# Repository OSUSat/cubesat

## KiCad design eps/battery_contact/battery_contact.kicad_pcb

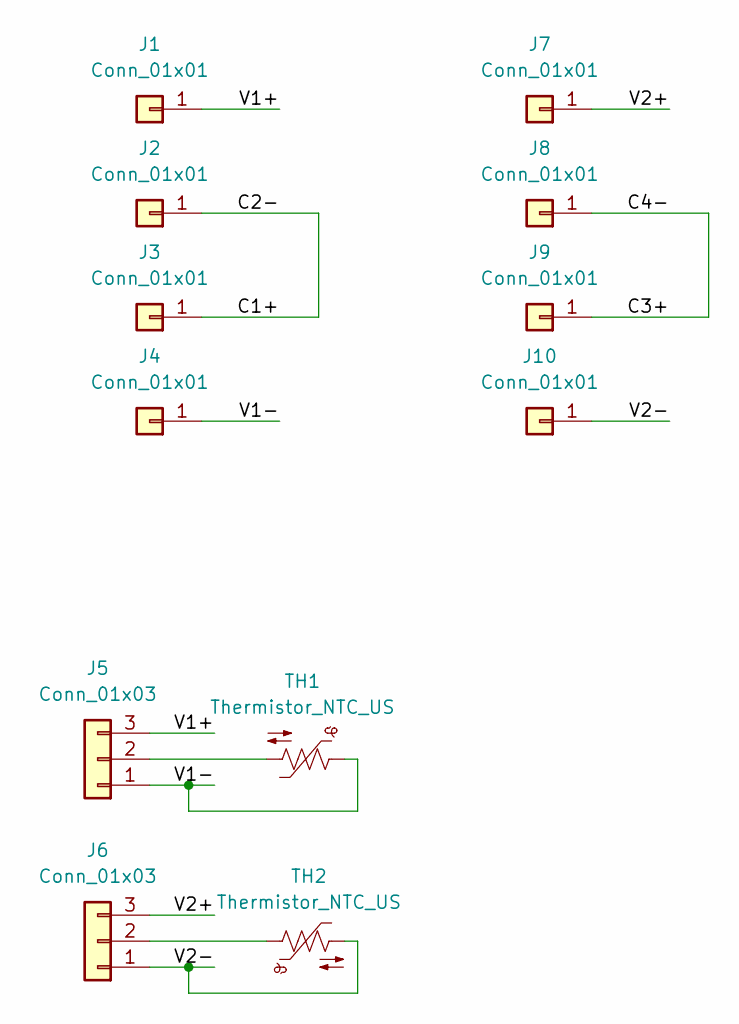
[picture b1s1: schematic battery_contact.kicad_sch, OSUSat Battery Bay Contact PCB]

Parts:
J1, J2, J3, J4, J7, J8, J9, J10: Conn_01x01; BAT_FB07
J5, J6: Conn_01x03; JST_PH_B3B-PH-K_1x03_P2.00mm_Vertical
TH1, TH2: Thermistor_NTC_US; R_0402_1005Metric

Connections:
/C1+: J2.1 (Pin_1_1), J3.1 (Pin_1_1)
/C3+: J8.1 (Pin_1_1), J9.1 (Pin_1_1)
/V1+: J1.1 (Pin_1_1), J5.3
/V1-: J4.1 (Pin_1_1), J5.1, TH1.1
/V2+: J6.3, J7.1 (Pin_1_1)
/V2-: J6.1, J10.1 (Pin_1_1), TH2.2
unnamed: J5.2, TH1.2
unnamed: J6.2, TH2.1

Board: 2 copper layers, 12 parts (0 on the bottom side), 8 nets, no tracks yet.

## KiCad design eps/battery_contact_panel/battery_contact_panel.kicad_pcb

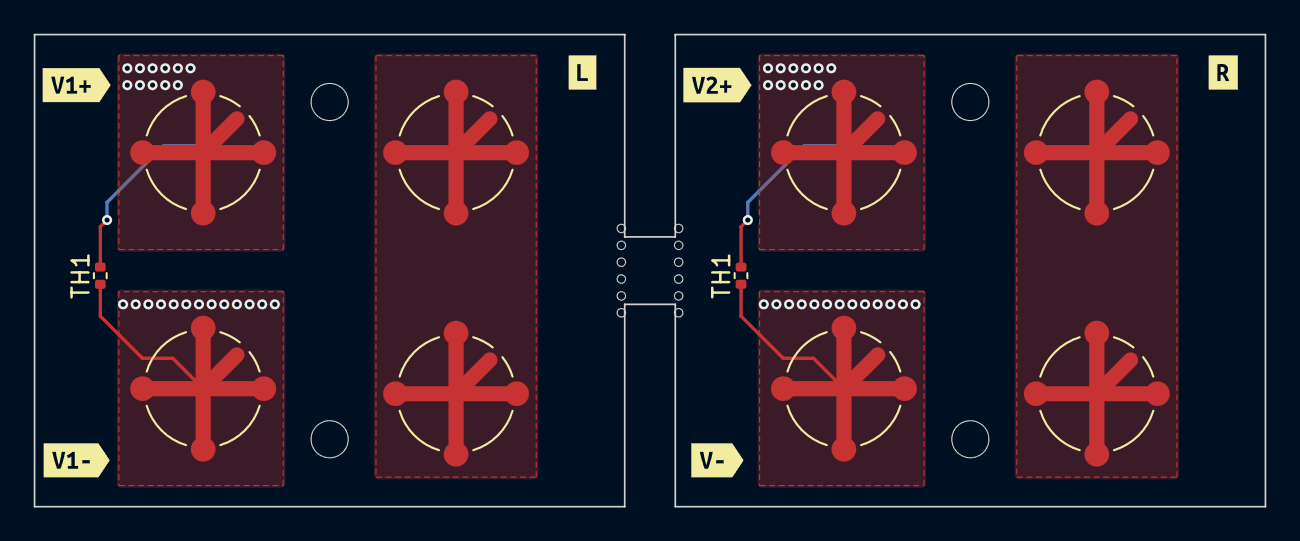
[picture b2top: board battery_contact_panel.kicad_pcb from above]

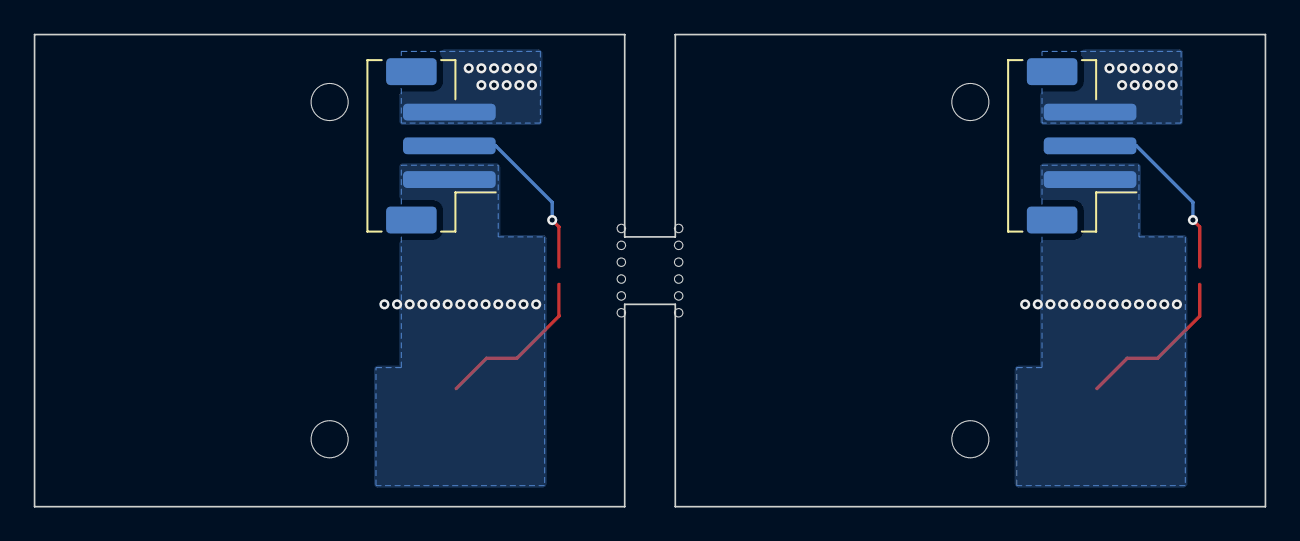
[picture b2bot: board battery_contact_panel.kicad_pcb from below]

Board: 2 copper layers, 73.0 x 28.0 mm, 34 parts (2 on the bottom side), 8 nets.

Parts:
H1, H1#2, H2, H2#2: MountingHole; MountingHole_2.2mm_M2
J1, J1#2, J2, J2#2, J4, J4#2, J7, J7#2: Conn_01x01; BAT_FB07
J5, J5#2: Conn_01x03; JST_PH_B3B-PH-SM4-TB_1x03-1MP_P2.00mm_Vertical
KiKit_MB_1_1, KiKit_MB_1_2, KiKit_MB_1_3, KiKit_MB_1_4, KiKit_MB_1_5, KiKit_MB_1_6, KiKit_MB_2_1, KiKit_MB_2_2, KiKit_MB_2_3, KiKit_MB_2_4, KiKit_MB_2_5, KiKit_MB_2_6: NPTH
TH1, TH1#2: Thermistor_NTC_US; R_0402_1005Metric
kibuzzard-6A263C7A: G***; kibuzzard-6A263C7A
kibuzzard-6A263D29: G***; kibuzzard-6A263D29
kibuzzard-6A2907CC: G***; kibuzzard-6A2907CC
kibuzzard-6A2907D5: G***; kibuzzard-6A2907D5
kibuzzard-6A2907E9: G***; kibuzzard-6A2907E9
kibuzzard-6A2907EF: G***; kibuzzard-6A2907EF

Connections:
Board_0-/C1+: J2.1 (Pin_1_1), J7#2.1 (Pin_1_1)
Board_0-/V1+: J1#2.1 (Pin_1_1), J5.3
Board_0-/V1-: J4#2.1 (Pin_1_1), J5.1, TH1.1
Board_0-Net-(J5-Pin_2): J5.2, TH1.2
Board_1-/C1+: J2#2.1 (Pin_1_1), J7.1 (Pin_1_1)
Board_1-/V1+: J1.1 (Pin_1_1), J5#2.3
Board_1-/V1-: J4.1 (Pin_1_1), J5#2.1, TH1#2.1
Board_1-Net-(J5-Pin_2): J5#2.2, TH1#2.2

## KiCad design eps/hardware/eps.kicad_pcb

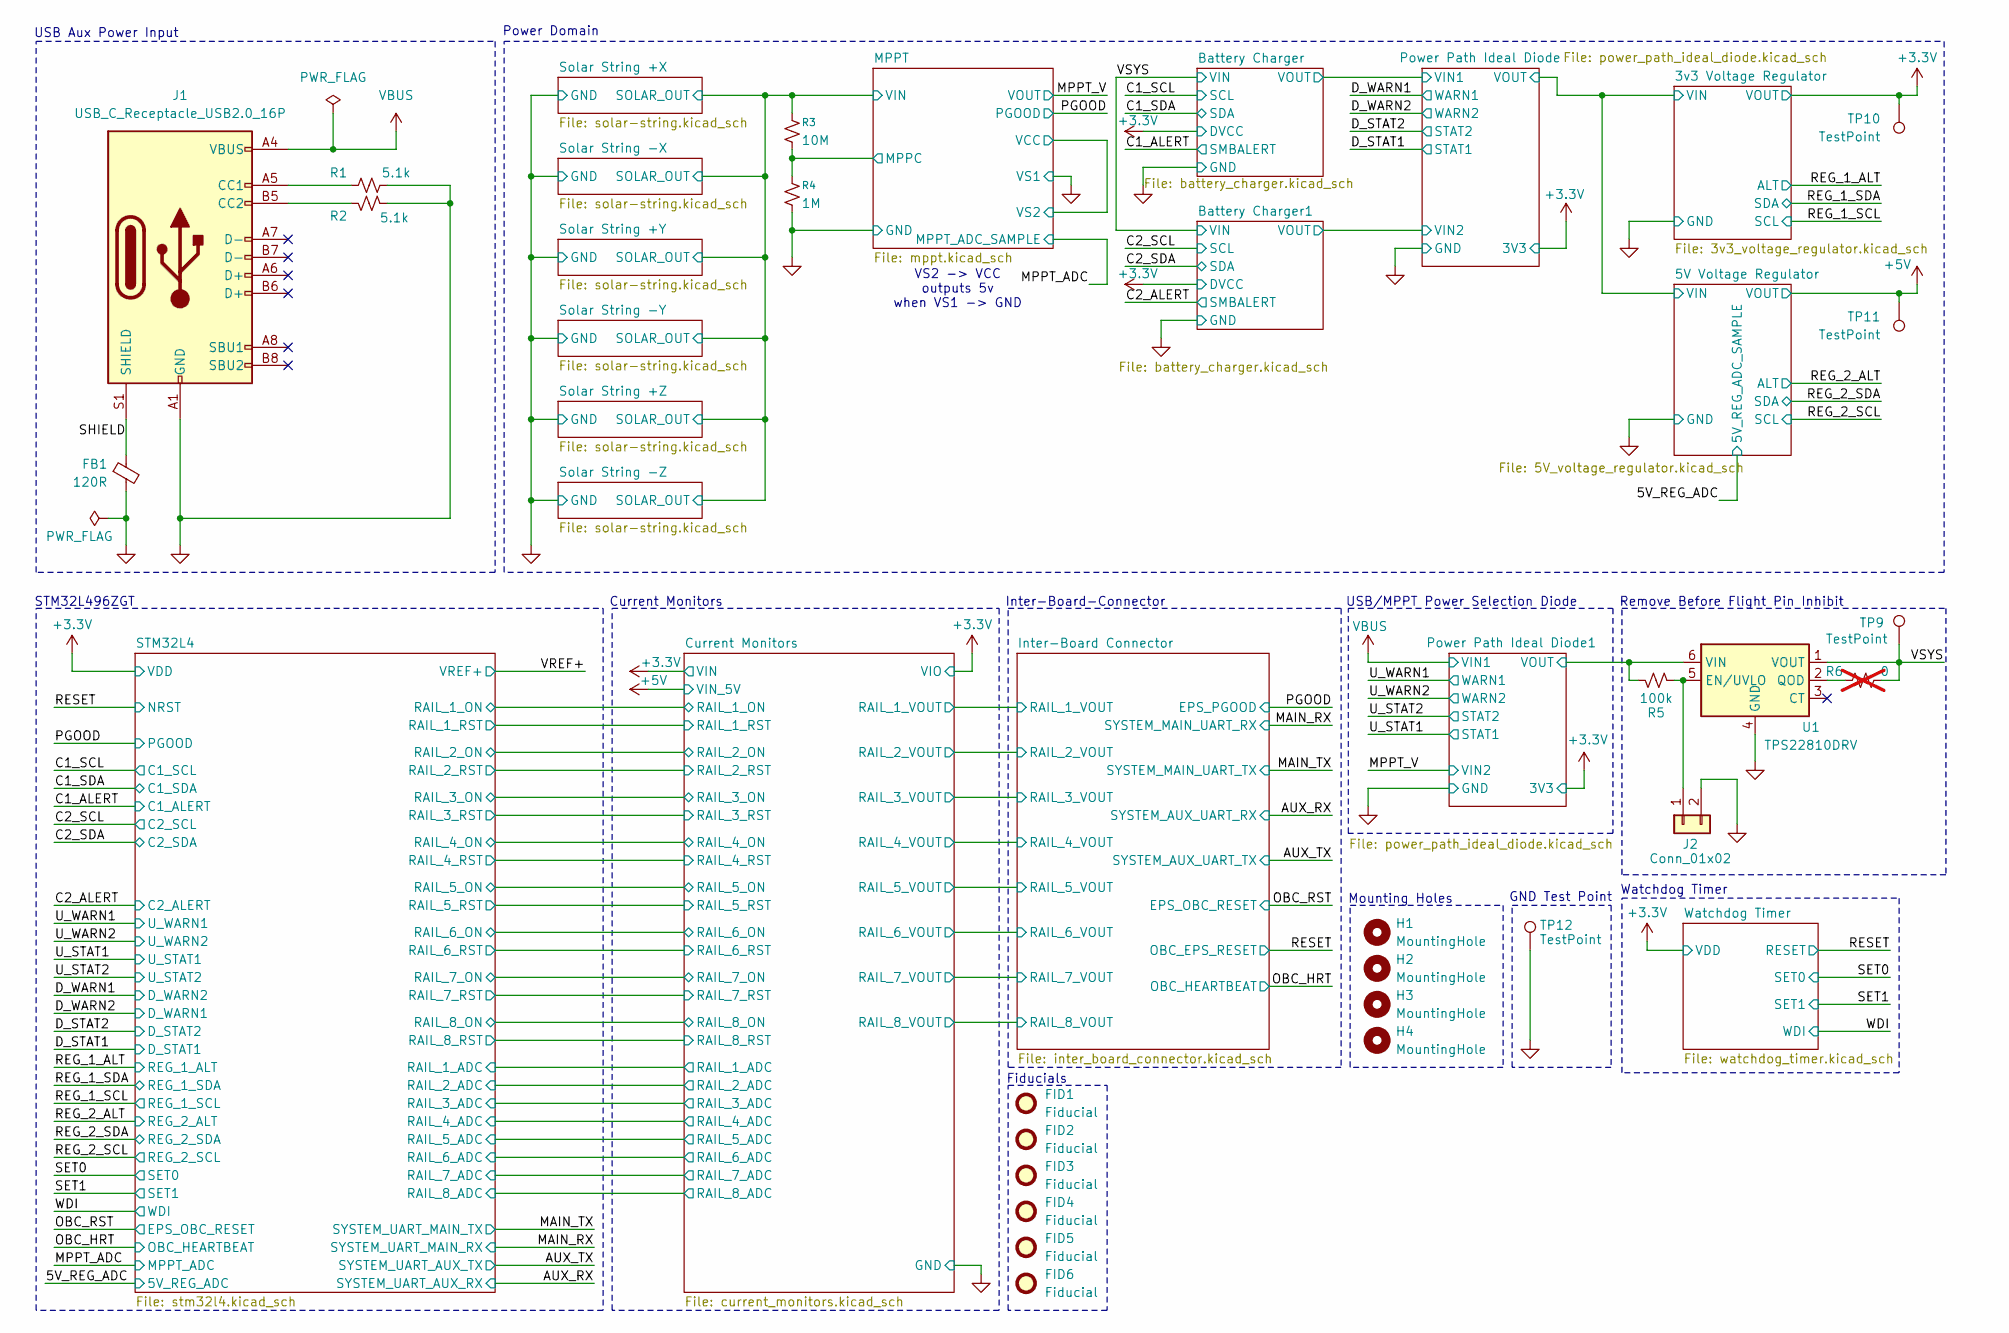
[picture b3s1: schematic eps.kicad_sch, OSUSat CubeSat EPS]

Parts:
FB1: 120R; L_0603_1608Metric
FID1, FID2, FID3, FID4, FID5, FID6: Fiducial; Fiducial_1mm_Mask2mm
H1, H2, H3, H4: MountingHole; MountingHole_3.2mm_M3
J1: USB_C_Receptacle_USB2.0_16P; USB_C_Receptacle_Palconn_UTC16-G
J2: Conn_01x02; PinHeader_1x02_P2.54mm_Vertical
R1, R2: 5.1k; R_0402_1005Metric
R3: 10M; R_0402_1005Metric
R4: 1M; R_0402_1005Metric
R5: 100k; R_0402_1005Metric
R6: 0; R_0402_1005Metric; not fitted
TP9, TP10, TP11, TP12: TestPoint; TestPoint_Pad_D1.0mm
U1: TPS22810DRV; WSON-6-1EP_2x2mm_P0.65mm_EP1x1.6mm

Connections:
+3.3V: TP10.1; also elsewhere on the board
+5V: TP11.1; also elsewhere on the board
/MPPT/MPPC: R3.2, R4.1; also elsewhere on the board
/MPPT/VIN: R3.1; also elsewhere on the board
/Power Path Ideal Diode1/VOUT: R5.2, U1.6 (VIN); also elsewhere on the board
/SHIELD: FB1.1, J1.S1 (SHIELD)
/VSYS: R6.2, TP9.1, U1.1 (VOUT); also elsewhere on the board
GND: FB1.2, J1.A1 (GND), J1.A12 (GND), J1.B1 (GND), J1.B12 (GND), J2.2, R1.2, R2.2, R4.2, TP12.1, U1.4 (GND), U1.7 (GND); also elsewhere on the board
unnamed: J1.A5 (CC1), R1.1
unnamed: J1.B5 (CC2), R2.1
unnamed: J2.1, R5.1, U1.5 (EN/UVLO)
unnamed: R6.1, U1.2 (QOD)
VBUS: J1.A4 (VBUS), J1.A9 (VBUS), J1.B4 (VBUS), J1.B9 (VBUS); also elsewhere on the board

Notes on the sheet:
Mounting Holes
VS2 -> VCC outputs 5v when VS1 -> GND
Inter-Board-Connector
Remove Before Flight Pin Inhibit
Watchdog Timer
GND Test Point
USB/MPPT Power Selection Diode
Current Monitors
Fiducials
Power Domain
STM32L496ZGT
USB Aux Power Input

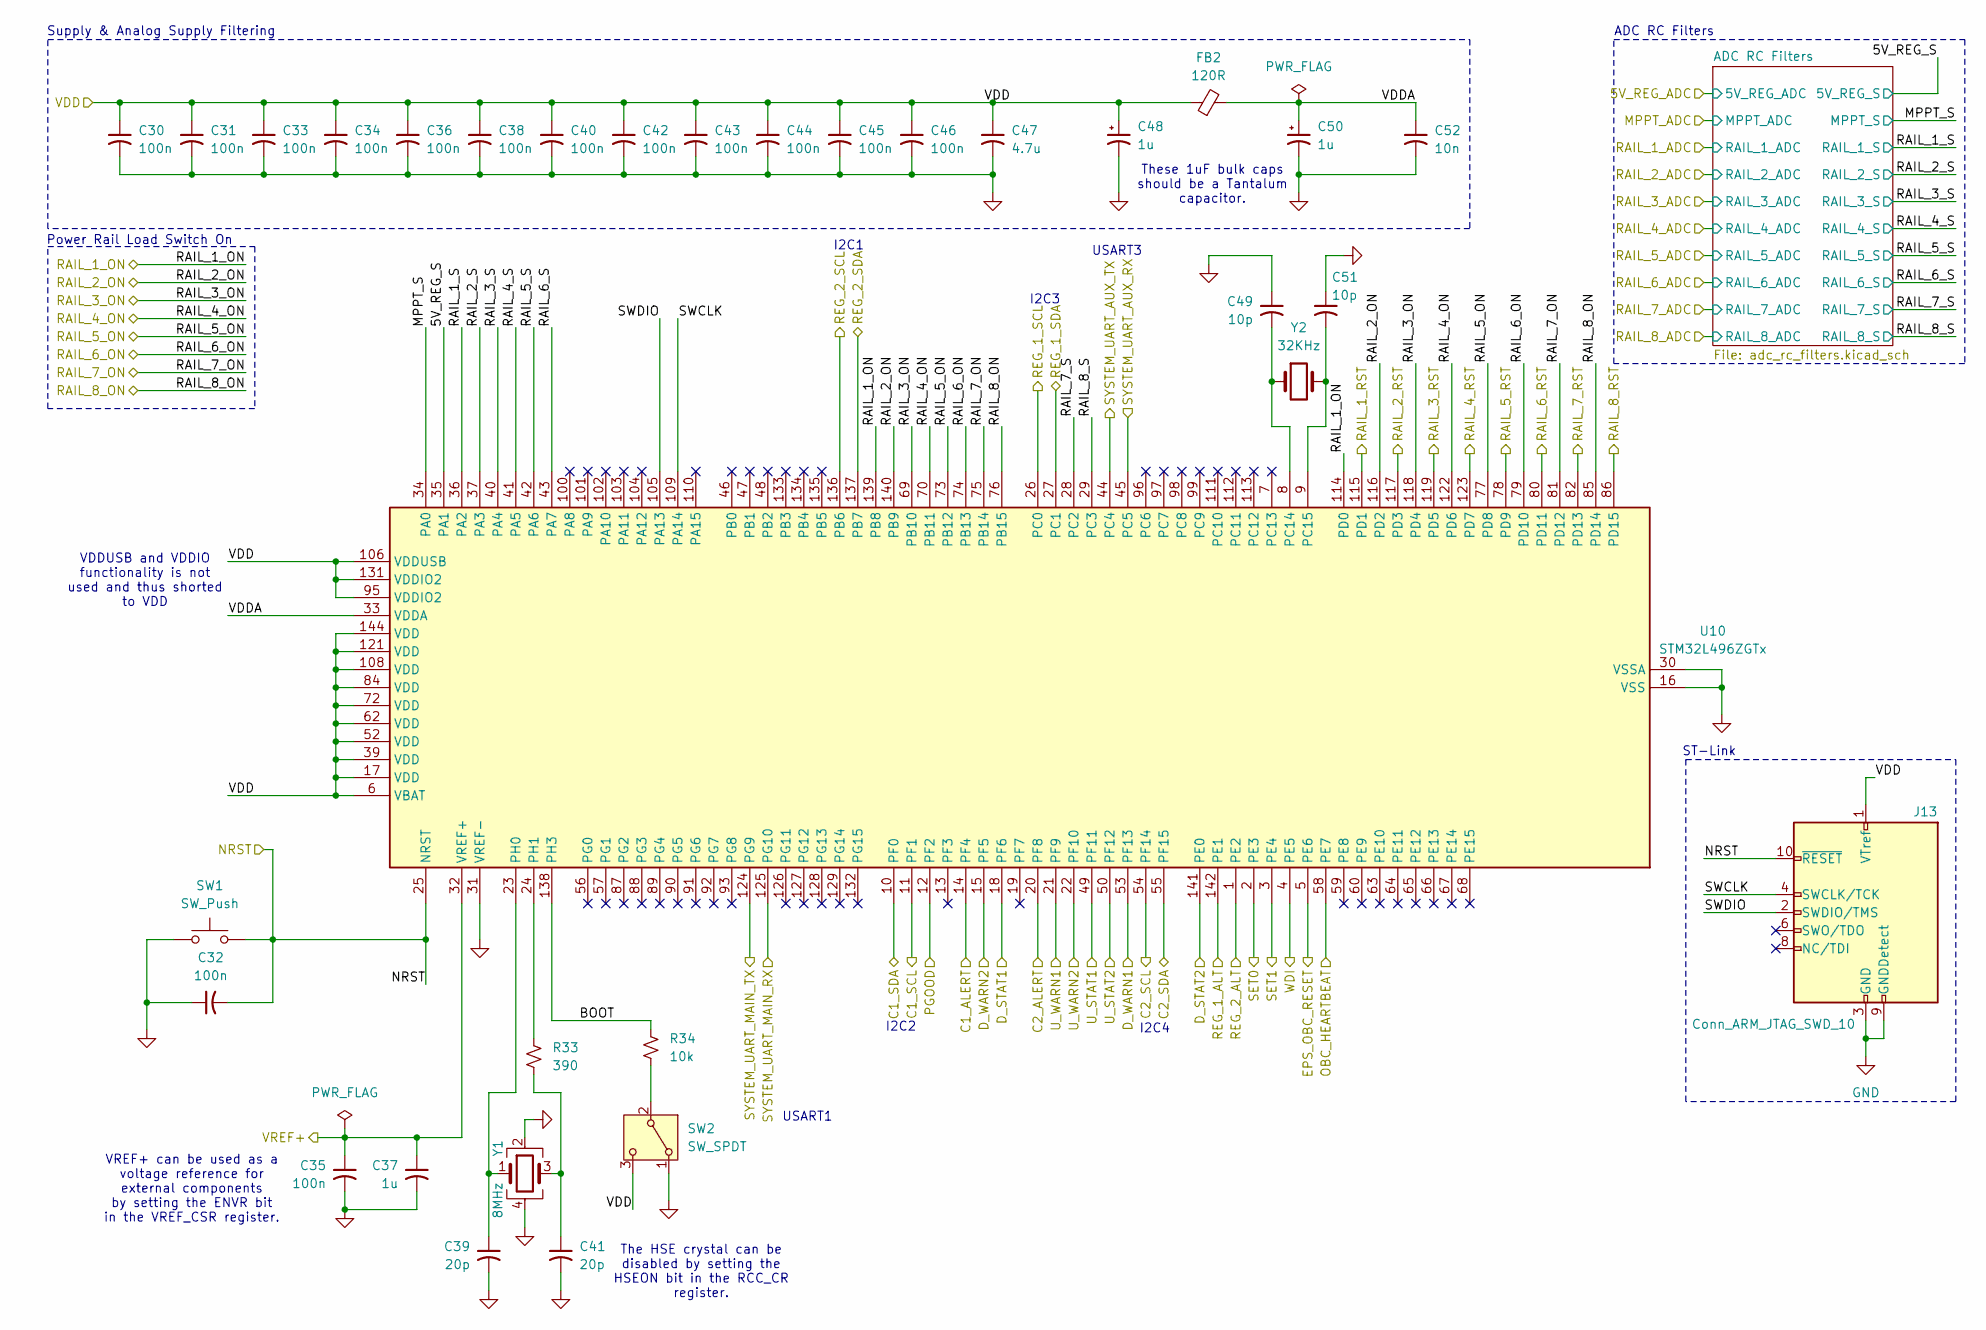
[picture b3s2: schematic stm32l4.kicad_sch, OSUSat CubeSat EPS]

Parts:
C30, C31, C32, C33, C34, C35, C36, C38, C40, C42, C43, C44, C45, C46: 100n; C_0402_1005Metric
C37: 1u; C_0402_1005Metric
C39, C41: 20p; C_0402_1005Metric
C47: 4.7u; C_0402_1005Metric
C48, C50: 1u; CP_EIA-3216-18_Kemet-A
C49, C51: 10p; C_0402_1005Metric
C52: 10n; C_0402_1005Metric
FB2: 120R; L_0603_1608Metric
J13: Conn_ARM_JTAG_SWD_10; PinHeader_2x05_P1.27mm_Vertical_SMD
R33: 390; R_0402_1005Metric
R34: 10k; R_0402_1005Metric
SW1: SW_Push; SW_Push_SPST_NO_Alps_SKRK
SW2: SW_SPDT; SW_SPDT_PCM12
U10: STM32L496ZGTx; LQFP-144_20x20mm_P0.5mm
Y1: 8MHz; Crystal_SMD_3225-4Pin_3.2x2.5mm; LCSC PN C9002
Y2: 32KHz; Crystal_SMD_3215-2Pin_3.2x1.5mm

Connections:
+3.3V: C30.1, C31.1, C33.1, C34.1, C36.1, C38.1, C40.1, C42.1, C43.1, C44.1, C45.1, C46.1, C47.1, C48.1, FB2.1, J13.1 (VTref), SW2.3 (C), U10.6 (VBAT), U10.17 (VDD), U10.39 (VDD), U10.52 (VDD), U10.62 (VDD), U10.72 (VDD), U10.84 (VDD), U10.95 (VDDIO2), U10.106 (VDDUSB), U10.108 (VDD), U10.121 (VDD), U10.131 (VDDIO2), U10.144 (VDD); also elsewhere on the board
/AUX_RX: U10.45 (PC5); also elsewhere on the board
/AUX_TX: U10.44 (PC4); also elsewhere on the board
/C1_ALERT: U10.14 (PF4); also elsewhere on the board
/C1_SCL: U10.11 (PF1); also elsewhere on the board
/C1_SDA: U10.10 (PF0); also elsewhere on the board
/C2_ALERT: U10.20 (PF8); also elsewhere on the board
/C2_SCL: U10.54 (PF14); also elsewhere on the board
/C2_SDA: U10.55 (PF15); also elsewhere on the board
/Current Monitors/RAIL_1_RST: U10.115 (PD1); also elsewhere on the board
/Current Monitors/RAIL_2_RST: U10.117 (PD3); also elsewhere on the board
/Current Monitors/RAIL_3_RST: U10.119 (PD5); also elsewhere on the board
/Current Monitors/RAIL_4_RST: U10.123 (PD7); also elsewhere on the board
/Current Monitors/RAIL_5_RST: U10.78 (PD9); also elsewhere on the board
/Current Monitors/RAIL_6_RST: U10.80 (PD11); also elsewhere on the board
/Current Monitors/RAIL_7_RST: U10.82 (PD13); also elsewhere on the board
/Current Monitors/RAIL_8_RST: U10.86 (PD15); also elsewhere on the board
/D_STAT1: U10.18 (PF6); also elsewhere on the board
/D_STAT2: U10.141 (PE0); also elsewhere on the board
/D_WARN1: U10.15 (PF5); also elsewhere on the board
/D_WARN2: U10.53 (PF13); also elsewhere on the board
/MAIN_RX: U10.125 (PG10); also elsewhere on the board
/MAIN_TX: U10.124 (PG9); also elsewhere on the board
/OBC_HRT: U10.58 (PE7); also elsewhere on the board
/OBC_RST: U10.5 (PE6); also elsewhere on the board
/PGOOD: U10.12 (PF2); also elsewhere on the board
/REG_1_ALT: U10.142 (PE1); also elsewhere on the board
/REG_1_SCL: U10.26 (PC0); also elsewhere on the board
/REG_1_SDA: U10.27 (PC1); also elsewhere on the board
/REG_2_ALT: U10.1 (PE2); also elsewhere on the board
/REG_2_SCL: U10.136 (PB6); also elsewhere on the board
/REG_2_SDA: U10.137 (PB7); also elsewhere on the board
/RESET: C32.2, J13.10 (~RESET), SW1.2, U10.25 (NRST); also elsewhere on the board
/SET0: U10.2 (PE3); also elsewhere on the board
/SET1: U10.3 (PE4); also elsewhere on the board
/STM32L4/5V_REG_S: U10.35 (PA1); also elsewhere on the board
/STM32L4/BOOT: R34.1, U10.138 (PH3)
/STM32L4/MPPT_S: U10.34 (PA0); also elsewhere on the board
/STM32L4/RAIL_1_ON: U10.114 (PD0), U10.139 (PB8); also elsewhere on the board
/STM32L4/RAIL_1_S: U10.36 (PA2); also elsewhere on the board
/STM32L4/RAIL_2_ON: U10.116 (PD2), U10.140 (PB9); also elsewhere on the board
/STM32L4/RAIL_2_S: U10.37 (PA3); also elsewhere on the board
/STM32L4/RAIL_3_ON: U10.69 (PB10), U10.118 (PD4); also elsewhere on the board
/STM32L4/RAIL_3_S: U10.40 (PA4); also elsewhere on the board
/STM32L4/RAIL_4_ON: U10.70 (PB11), U10.122 (PD6); also elsewhere on the board
/STM32L4/RAIL_4_S: U10.41 (PA5); also elsewhere on the board
/STM32L4/RAIL_5_ON: U10.73 (PB12), U10.77 (PD8); also elsewhere on the board
/STM32L4/RAIL_5_S: U10.42 (PA6); also elsewhere on the board
/STM32L4/RAIL_6_ON: U10.74 (PB13), U10.79 (PD10); also elsewhere on the board
/STM32L4/RAIL_6_S: U10.43 (PA7); also elsewhere on the board
/STM32L4/RAIL_7_ON: U10.75 (PB14), U10.81 (PD12); also elsewhere on the board
/STM32L4/RAIL_7_S: U10.28 (PC2); also elsewhere on the board
/STM32L4/RAIL_8_ON: U10.76 (PB15), U10.85 (PD14); also elsewhere on the board
/STM32L4/RAIL_8_S: U10.29 (PC3); also elsewhere on the board
/STM32L4/SWCLK: J13.4 (SWCLK/TCK), U10.109 (PA14)
/STM32L4/SWDIO: J13.2 (SWDIO/TMS), U10.105 (PA13)
/STM32L4/VDDA: C50.1, C52.1, FB2.2, U10.33 (VDDA)
/U_STAT1: U10.49 (PF11); also elsewhere on the board
/U_STAT2: U10.50 (PF12); also elsewhere on the board
/U_WARN1: U10.21 (PF9); also elsewhere on the board
/U_WARN2: U10.22 (PF10); also elsewhere on the board
/VREF+: C35.1, C37.1, U10.32 (VREF+)
/WDI: U10.4 (PE5); also elsewhere on the board
GND: C30.2, C31.2, C32.1, C33.2, C34.2, C35.2, C36.2, C37.2, C38.2, C39.2, C40.2, C41.2, C42.2, C43.2, C44.2, C45.2, C46.2, C47.2, C48.2, C49.1, C50.2, C51.1, C52.2, J13.3 (GND), J13.5 (GND), J13.9 (GNDDetect), SW1.1, SW2.1 (A), U10.16 (VSS), U10.30 (VSSA), U10.31 (VREF-), U10.38 (VSS), U10.51 (VSS), U10.61 (VSS), U10.71 (VSS), U10.83 (VSS), U10.94 (VSS), U10.107 (VSS), U10.120 (VSS), U10.130 (VSS), U10.143 (VSS), Y1.2, Y1.4; also elsewhere on the board
unnamed: C41.1, R33.2, Y1.3
unnamed: R34.2, SW2.2 (B)
unnamed: C49.2, U10.8 (PC14), Y2.1
unnamed: C51.2, U10.9 (PC15), Y2.2
unnamed: C39.1, U10.23 (PH0), Y1.1
unnamed: R33.1, U10.24 (PH1)

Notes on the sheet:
USART3
VREF+ can be used as a voltage reference for external components by setting the ENVR bit in the VREF_CSR register.
The HSE crystal can be disabled by setting the HSEON bit in the RCC_CR register.
ADC RC Filters
I2C3
These 1uF bulk caps should be a Tantalum capacitor.
Supply & Analog Supply Filtering
I2C4
VDDUSB and VDDIO functionality is not used and thus shorted to VDD
ST-Link
I2C2
I2C1
Power Rail Load Switch On
USART1

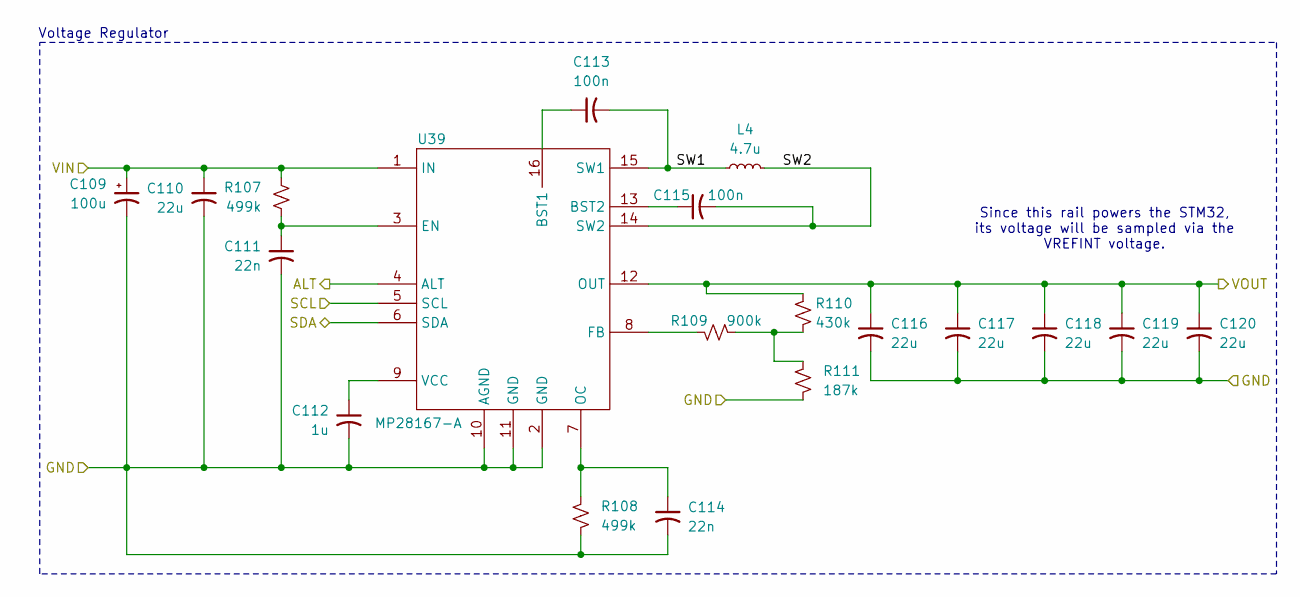
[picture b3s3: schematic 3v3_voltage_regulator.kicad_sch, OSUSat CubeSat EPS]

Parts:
C109: 100u; CP_EIA-3216-18_Kemet-A
C110, C116, C117, C118, C119, C120: 22u; C_0402_1005Metric
C111, C114: 22n; C_0402_1005Metric
C112: 1u; C_0402_1005Metric
C113, C115: 100n; C_0402_1005Metric
L4: 4.7u; L_Vishay_IHLP-2020
R107, R108: 499k; R_0402_1005Metric
R109: 900k; R_0402_1005Metric
R110: 430k; R_0402_1005Metric
R111: 187k; R_0402_1005Metric
U39: MP28167-A; MPS_QFN-16_3x3mm_P0.5mm

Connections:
+3.3V: C116.1, C117.1, C118.1, C119.1, C120.1, R110.1, U39.12 (OUT); also elsewhere on the board
/3v3 Voltage Regulator/SW1: C113.2, L4.1, U39.15 (SW1)
/3v3 Voltage Regulator/SW2: C115.2, L4.2, U39.14 (SW2)
/3v3 Voltage Regulator/VIN: C109.1, C110.1, R107.1, U39.1 (IN); also elsewhere on the board
/REG_1_ALT: U39.4 (ALT); also elsewhere on the board
/REG_1_SCL: U39.5 (SCL); also elsewhere on the board
/REG_1_SDA: U39.6 (SDA); also elsewhere on the board
GND: C109.2, C110.2, C111.2, C112.2, C114.2, C116.2, C117.2, C118.2, C119.2, C120.2, R108.2, R111.2, U39.2 (GND), U39.10 (AGND), U39.11 (GND); also elsewhere on the board
unnamed: R109.2, R110.2, R111.1
unnamed: C113.1, U39.16 (BST1)
unnamed: C115.1, U39.13 (BST2)
unnamed: C111.1, R107.2, U39.3 (EN)
unnamed: R109.1, U39.8 (FB)
unnamed: C114.1, R108.1, U39.7 (OC)
unnamed: C112.1, U39.9 (VCC)

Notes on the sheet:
Since this rail powers the STM32, its voltage will be sampled via the VREFINT voltage.
Voltage Regulator

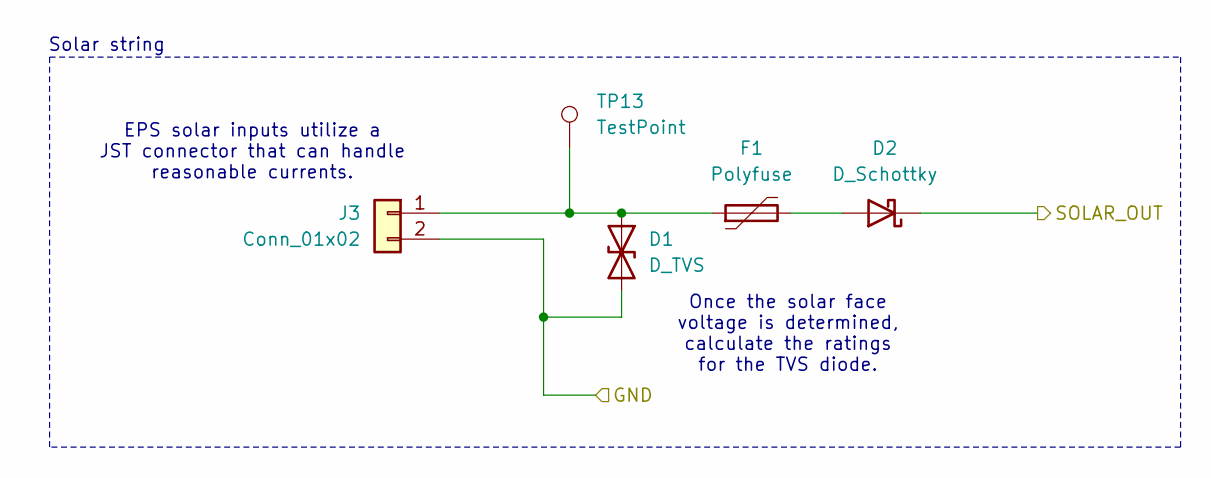
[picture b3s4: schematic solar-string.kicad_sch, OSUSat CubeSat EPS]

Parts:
D1: D_TVS; D_SOD-523
D2: D_Schottky; D_SOD-323
F1: Polyfuse; Fuse_0402_1005Metric
J3: Conn_01x02; JST_PH_B2B-PH-K_1x02_P2.00mm_Vertical
TP13: TestPoint; TestPoint_Pad_D1.0mm

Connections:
/MPPT/VIN: D2.1 (K); also elsewhere on the board
GND: D1.2 (A2), J3.2; also elsewhere on the board
unnamed: D1.1 (A1), F1.1, J3.1, TP13.1
unnamed: D2.2 (A), F1.2

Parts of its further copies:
D3, D5, D7, D9, D11: D_TVS; D_SOD-523
D4, D6, D8, D10, D12: D_Schottky; D_SOD-323
F2, F3, F4, F5, F6: Polyfuse; Fuse_0402_1005Metric
J4, J5, J6, J7, J8: Conn_01x02; JST_PH_B2B-PH-K_1x02_P2.00mm_Vertical
TP14, TP15, TP16, TP17, TP18: TestPoint; TestPoint_Pad_D1.0mm

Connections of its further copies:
/MPPT/VIN: D4.1 (K), D6.1 (K), D8.1 (K), D10.1 (K), D12.1 (K); also elsewhere on the board
GND: D3.2 (A2), D5.2 (A2), D7.2 (A2), D9.2 (A2), D11.2 (A2), J4.2, J5.2, J6.2, J7.2, J8.2; also elsewhere on the board
unnamed: D3.1 (A1), F2.1, J4.1, TP14.1
unnamed: D4.2 (A), F2.2
unnamed: D5.1 (A1), F3.1, J5.1, TP15.1
unnamed: D6.2 (A), F3.2
unnamed: D7.1 (A1), F4.1, J6.1, TP16.1
unnamed: D8.2 (A), F4.2
unnamed: D9.1 (A1), F5.1, J7.1, TP17.1
unnamed: D10.2 (A), F5.2
unnamed: D11.1 (A1), F6.1, J8.1, TP18.1
unnamed: D12.2 (A), F6.2

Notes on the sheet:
Once the solar face voltage is determined, calculate the ratings for the TVS diode.
EPS solar inputs utilize a JST connector that can handle reasonable currents.
Solar string

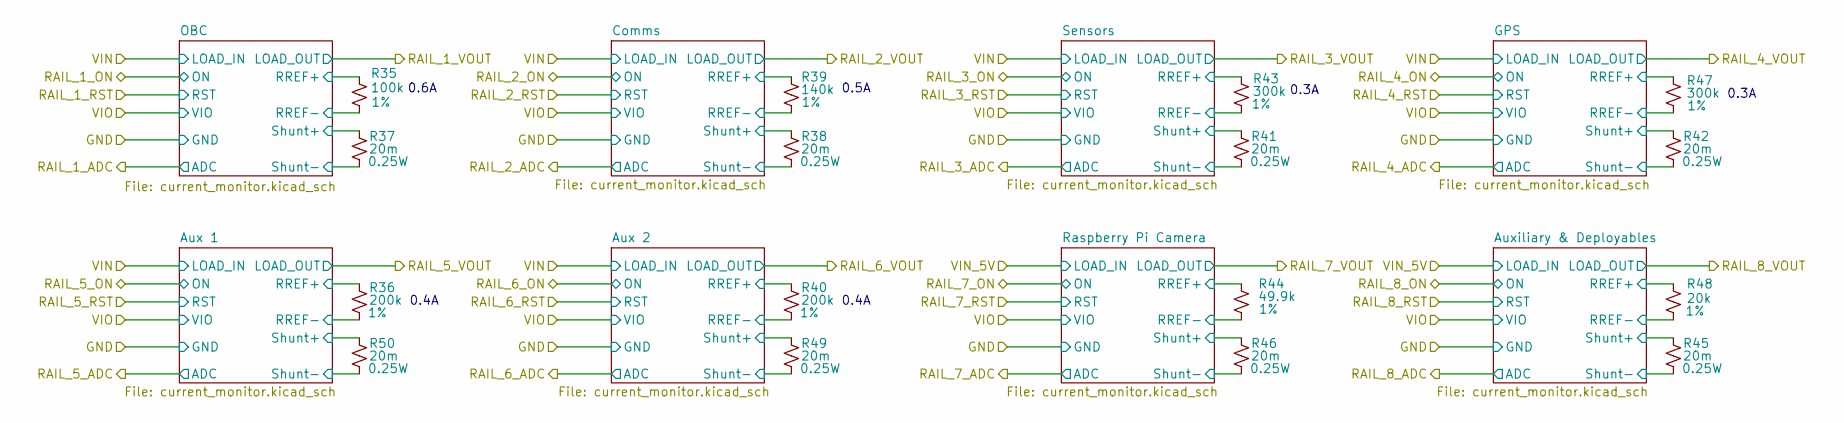
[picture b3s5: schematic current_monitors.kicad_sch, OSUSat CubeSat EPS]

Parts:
R35: 100k; R_0402_1005Metric; Tolerance 1%
R36, R40: 200k; R_0402_1005Metric; Tolerance 1%
R37, R38, R41, R42, R45, R46, R49, R50: 20m; R_1206_3216Metric; LCSC PN C465512
R39: 140k; R_0402_1005Metric; Tolerance 1%
R43, R47: 300k; R_0402_1005Metric; Tolerance 1%
R44: 49.9k; R_0402_1005Metric; Tolerance 1%
R48: 20k; R_0402_1005Metric; Tolerance 1%

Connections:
/Current Monitors/Aux 1/RREF+: R36.1; also elsewhere on the board
/Current Monitors/Aux 1/RREF-: R36.2; also elsewhere on the board
/Current Monitors/Aux 1/Shunt+: R50.1; also elsewhere on the board
/Current Monitors/Aux 1/Shunt-: R50.2; also elsewhere on the board
/Current Monitors/Aux 2/RREF+: R40.1; also elsewhere on the board
/Current Monitors/Aux 2/RREF-: R40.2; also elsewhere on the board
/Current Monitors/Aux 2/Shunt+: R49.1; also elsewhere on the board
/Current Monitors/Aux 2/Shunt-: R49.2; also elsewhere on the board
/Current Monitors/Auxiliary & Deployables/RREF+: R48.1; also elsewhere on the board
/Current Monitors/Auxiliary & Deployables/RREF-: R48.2; also elsewhere on the board
/Current Monitors/Auxiliary & Deployables/Shunt+: R45.1; also elsewhere on the board
/Current Monitors/Auxiliary & Deployables/Shunt-: R45.2; also elsewhere on the board
/Current Monitors/Comms/RREF+: R39.1; also elsewhere on the board
/Current Monitors/Comms/RREF-: R39.2; also elsewhere on the board
/Current Monitors/Comms/Shunt+: R38.1; also elsewhere on the board
/Current Monitors/Comms/Shunt-: R38.2; also elsewhere on the board
/Current Monitors/GPS/RREF+: R47.1; also elsewhere on the board
/Current Monitors/GPS/RREF-: R47.2; also elsewhere on the board
/Current Monitors/GPS/Shunt+: R42.1; also elsewhere on the board
/Current Monitors/GPS/Shunt-: R42.2; also elsewhere on the board
/Current Monitors/OBC/RREF+: R35.1; also elsewhere on the board
/Current Monitors/OBC/RREF-: R35.2; also elsewhere on the board
/Current Monitors/OBC/Shunt+: R37.1; also elsewhere on the board
/Current Monitors/OBC/Shunt-: R37.2; also elsewhere on the board
/Current Monitors/Raspberry Pi Camera/RREF+: R44.1; also elsewhere on the board
/Current Monitors/Raspberry Pi Camera/RREF-: R44.2; also elsewhere on the board
/Current Monitors/Raspberry Pi Camera/Shunt+: R46.1; also elsewhere on the board
/Current Monitors/Raspberry Pi Camera/Shunt-: R46.2; also elsewhere on the board
/Current Monitors/Sensors/RREF+: R43.1; also elsewhere on the board
/Current Monitors/Sensors/RREF-: R43.2; also elsewhere on the board
/Current Monitors/Sensors/Shunt+: R41.1; also elsewhere on the board
/Current Monitors/Sensors/Shunt-: R41.2; also elsewhere on the board

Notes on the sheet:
0.4A
0.3A
0.6A
0.5A

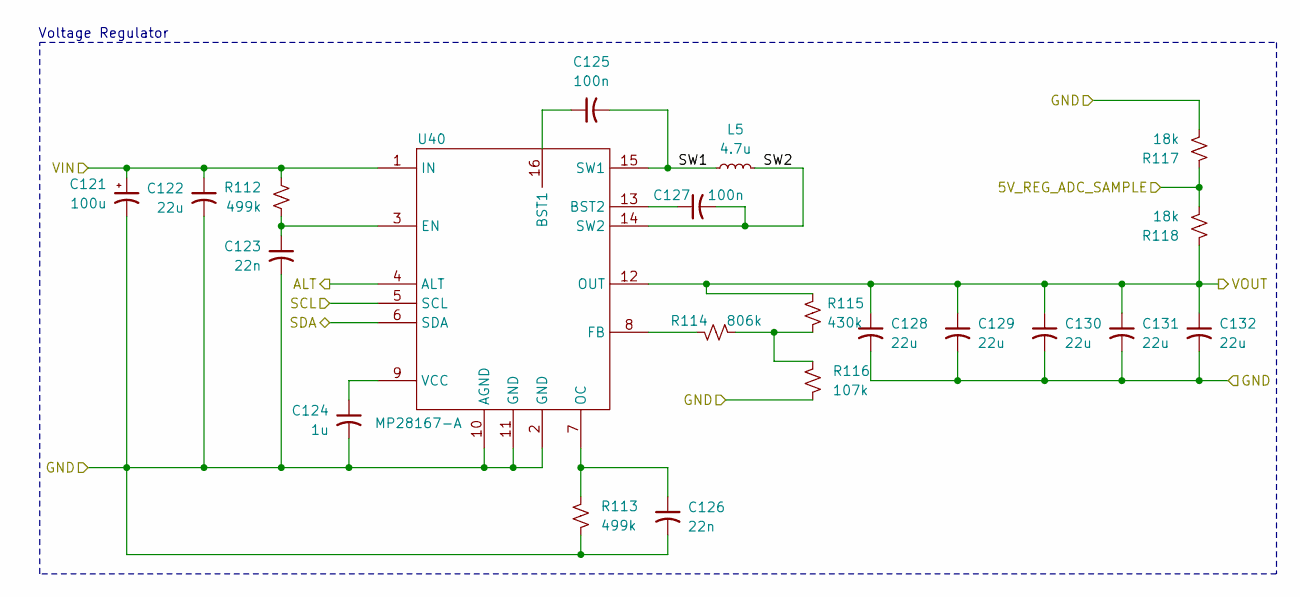
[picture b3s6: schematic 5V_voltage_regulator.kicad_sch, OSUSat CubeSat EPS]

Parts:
C121: 100u; CP_EIA-3216-18_Kemet-A
C122, C128, C129, C130, C131, C132: 22u; C_0402_1005Metric
C123, C126: 22n; C_0402_1005Metric
C124: 1u; C_0402_1005Metric
C125, C127: 100n; C_0402_1005Metric
L5: 4.7u; L_Vishay_IHLP-2020
R112, R113: 499k; R_0402_1005Metric
R114: 806k; R_0402_1005Metric
R115: 430k; R_0402_1005Metric
R116: 107k; R_0402_1005Metric
R117, R118: 18k; R_0402_1005Metric
U40: MP28167-A; MPS_QFN-16_3x3mm_P0.5mm

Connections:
+5V: C128.1, C129.1, C130.1, C131.1, C132.1, R115.1, R118.1, U40.12 (OUT); also elsewhere on the board
/3v3 Voltage Regulator/VIN: C121.1, C122.1, R112.1, U40.1 (IN); also elsewhere on the board
/5V Voltage Regulator/SW1: C125.2, L5.1, U40.15 (SW1)
/5V Voltage Regulator/SW2: C127.2, L5.2, U40.14 (SW2)
/5V_REG_ADC: R117.1, R118.2; also elsewhere on the board
/REG_2_ALT: U40.4 (ALT); also elsewhere on the board
/REG_2_SCL: U40.5 (SCL); also elsewhere on the board
/REG_2_SDA: U40.6 (SDA); also elsewhere on the board
GND: C121.2, C122.2, C123.2, C124.2, C126.2, C128.2, C129.2, C130.2, C131.2, C132.2, R113.2, R116.2, R117.2, U40.2 (GND), U40.10 (AGND), U40.11 (GND); also elsewhere on the board
unnamed: R114.2, R115.2, R116.1
unnamed: C125.1, U40.16 (BST1)
unnamed: C127.1, U40.13 (BST2)
unnamed: C123.1, R112.2, U40.3 (EN)
unnamed: R114.1, U40.8 (FB)
unnamed: C126.1, R113.1, U40.7 (OC)
unnamed: C124.1, U40.9 (VCC)

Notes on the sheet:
Voltage Regulator
